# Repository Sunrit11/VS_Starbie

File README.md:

<<<<<<< Updated upstream

Very Simple Starbie 
created as the first week project of Half Life
a desktop pet gadget 
has a oled screen, 2 switches, MPU sensor, DHT sensor and LEDs
=======
Very Simple Starbie created as the first week project of Half Life a desktop pet gadget has a oled screen, 2 switches, MPU sensor, DHT sensor and LEDs

this is how the pcb looks  

>>>>>>> Stashed changes

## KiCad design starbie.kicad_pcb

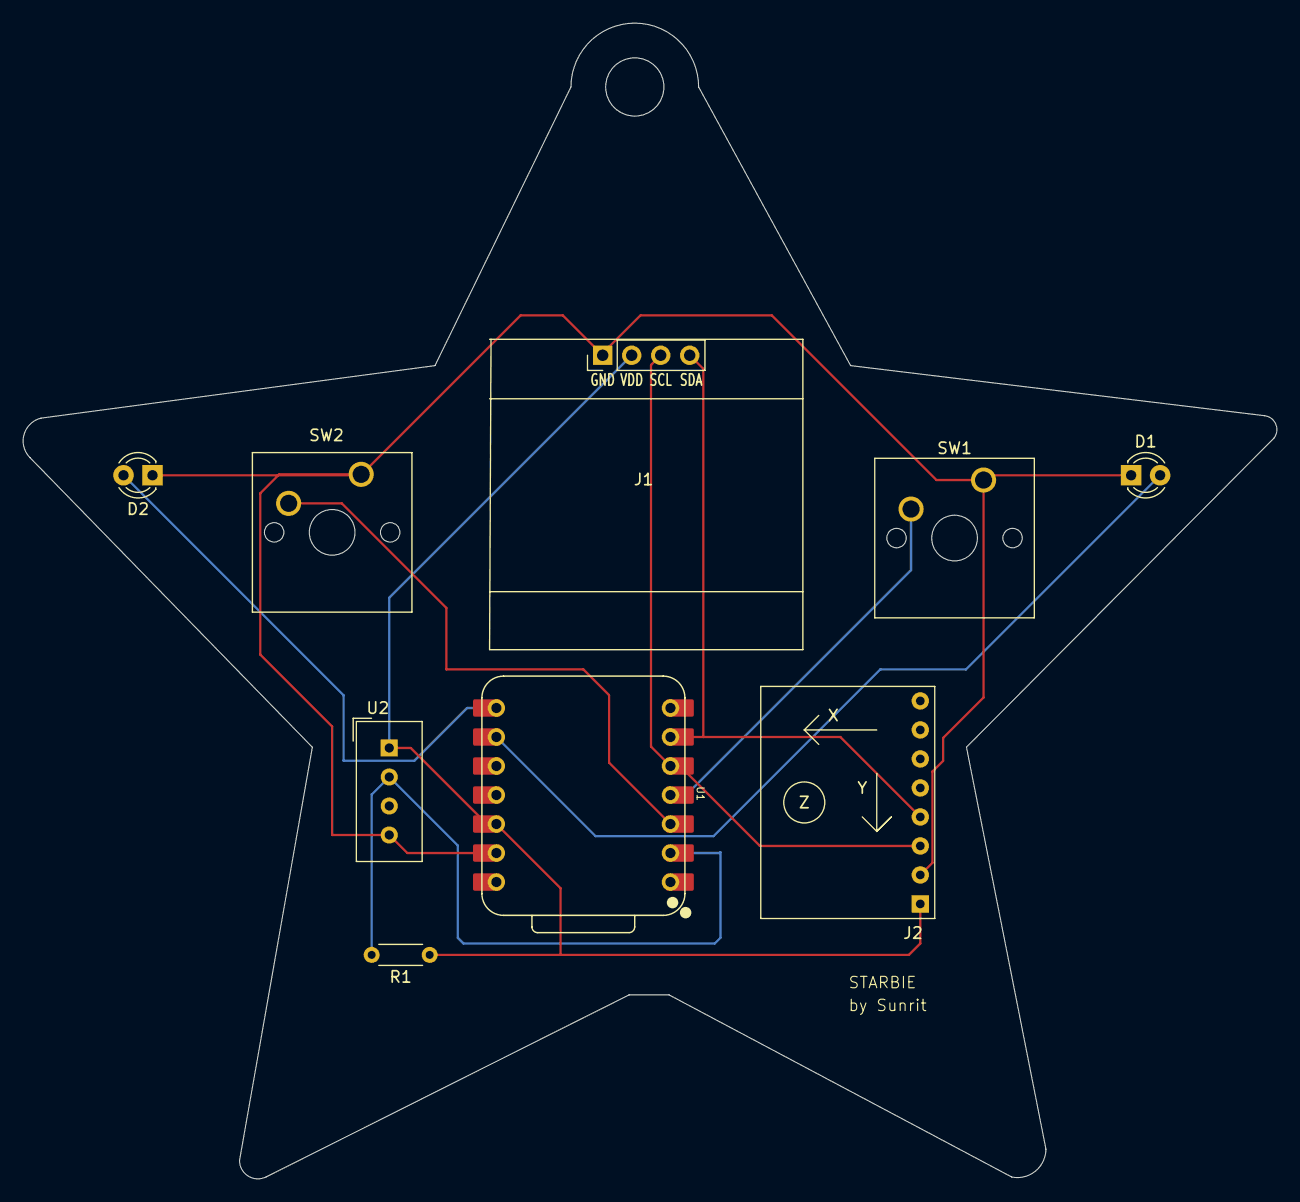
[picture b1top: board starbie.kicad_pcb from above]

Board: 2 copper layers, 109.8 x 101.2 mm, 9 parts (0 on the bottom side), 9 nets.

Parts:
D1, D2: LED; LED_D3.0mm
J1: Conn_01x04_Pin; Display_128x64_096_I2C
J2: Conn_01x08_Pin; MPU6050_Module
R1: 10k; R_Axial_DIN0204_L3.6mm_D1.6mm_P5.08mm_Horizontal
SW1, SW2: SW_Push; SW_Cherry_MX_1.00u_PCB
U1: XIAO-ESP32-C3-SMD; XIAO-ESP32-C6-DIP
U2: DHT11; Aosong_DHT11_5.5x12.0_P2.54mm

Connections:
+3.3V: J1.2, J2.1, R1.1, U1.12 (3V3_OUT), U2.1 (VDD)
GND: D1.1 (K), D2.1 (K), J1.1, J2.2, SW1.1, SW2.1, U1.13 (GND), U2.4 (GND)
unnamed: D1.2 (A), U1.9 (D8)
unnamed: D2.2 (A), U1.8 (D7)
unnamed: J1.3, J2.3, U1.5 (D4)
unnamed: J1.4, J2.4, U1.6 (D5)
unnamed: R1.2, U1.2 (D1), U2.2 (DATA)
unnamed: SW2.2, U1.3 (D2)
unnamed: SW1.2, U1.4 (D3)
